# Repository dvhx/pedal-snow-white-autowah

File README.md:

# pedal-snow-white-autowah
Snow White AutoWah (envelope filter) guitar pedal in 125B enclosure using layout without offboard-wiring

# Features

- 125B enclosure
- Top mounted jacks
- Center-negative DC barrel jack
- Perfect pedal layout:
    - one big pcb
    - no offboard wiring
    - easy insertion into enclosure
    - easy testing outside of enclosure (including pots and stomp switch!)
- Included:
    - KiCad 7 project (schematic, PCB, pot daugterboards)
    - Gerber files
    - Artwork

# Sample

- [Short sample on Youtube](https://www.youtube.com/embed/3BYL_riq4po)

# Schematic

# PCB

# Gerbers

- [gerbers.zip](https://raw.githubusercontent.com/dvhx/pedal-snow-white-autowah/refs/heads/master/kicad/gerbers.zip) - main PCB
- [gerbers-pots.zip](https://raw.githubusercontent.com/dvhx/pedal-snow-white-autowah/refs/heads/master/kicad_pot_daugterboard/gerbers-pots.zip) - pot daugterboards (you can also use perfboard or stripboard)

# BOM

Most of the parts is available at LCSC. At [https://www.lcsc.com/bom](https://www.lcsc.com/bom) you can import
this CSV file: [kicad/bom/bom_lcsc_autowah.csv](kicad/bom/bom_lcsc_autowah.csv), the price is approx. $17,
if you are building more than 1 pedal increase the amount of LM13700, audio jacks and opamps.
All other parts should be enough for 5 pedals due to minimal ordering quantity.

The rest of the parts is available on aliexpress:

- [50kB Pot, $0.80/pcs](https://s.click.aliexpress.com/e/_c3w9c93V)
- [1MC Pot, $0.80/pcs](https://s.click.aliexpress.com/e/_c3w9c93V)
- [50kB Pot, $0.80/pcs](https://s.click.aliexpress.com/e/_c3w9c93V)
- [100kB Pot, $0.80/pcs](https://s.click.aliexpress.com/e/_c3w9c93V)
- [Pot knobs, $1/10pcs](https://s.click.aliexpress.com/e/_c4n3mVNp)
- [2x Lightpipe, $0.285/pcs](https://www.aliexpress.com/item/1005010409920827.html)
- [Model Enclosure_125B, $7.85/pcs](https://s.click.aliexpress.com/e/_c33GoZ8r)
- [Switch_3P2T Switch_3PDT, $2.13/pcs](https://s.click.aliexpress.com/e/_c2vpDqzN)
- [0805 resistor kit, $4.18/1500pcs/60values](https://s.click.aliexpress.com/e/_c4WAuc7p)
- [0805 capacitor kit, $4.51/720pcs/36values](https://s.click.aliexpress.com/e/_c3UD8Gzd)

Total parts cost including shipping, PCB manufacturing, enclosure, spray paint and artwork sticker is approx $50.

# Photos

## PCB

## Enclosure

# Build instructions

- Visually check PCB for defects
- Chect for short on tip and sleeve pins of JDC1
- Power section
    - Solder GND wire loop connector (0.5~0.8mm tined copper wire) in top-right corner, it is used for crocodile clip on negative lead of multimeter
    - Solder JDC1 barrel jack connector and measure 9V on R96 pads against ground (note that this PCB uses center negative 9V DC connector)
    - Solder R96 10R (values 0-47R are ok, expected load is 15mA so voltage drop is R*0.015, e.g. 10R = 0.15V drop (from 9V), 47R=0.47V)
    - Polarity protection
        - Solder Q99 AO3401, marking A19T (P-ch mosfet)
        - Solder ZD99 9.1V zenner BZT52B9V1S, marking 2WE (any zenner from 3-12V can be used), line is cathode = tip of the white triangle
        - Solder R99 10k (some recommend 100k, with 10k reverse transient is shorter and smaller, but forward current draw is higher, depending on zener)
        - Test polarity protection
            - Connect regulated power supply via JDC1. Use one ammeter (in series) and one voltmeter (negative lead to GND loop testpoint, positive lead to + pin of LED D99)
            - Start at 0V and slowly rise the voltage to 9V, the voltage on D99 should closely follow the input voltage.
                 Current should be small as there is no load, few microamps.
                 Depenging on your zener it can be up to Vin/R99, e.g. at 9V/10k=900uA, mine was 400uA with 10k R99
            - Return to 0V and raise negative voltage to -9V. Output should be 0V (I have -0.07V, probably leakage of zener diode, mosfet and voltmeter itself).
            - When you try positive voltage now it should still works.
    - In front of the JDC1 there are 2 holes, you can solder 0.5mm tined copper wire loop across and over the top of the JDC1 connector to reduce the side-to-side strain
    - Solder "Power on" red LED D99 and it's current limiting resistor R98 (4k7).
    - Power it via ammeter (consumption could be 1.5mA), test point +9V (next to C99) should have approx. 9V
    - Power it with reverse polarity, current should be zero, voltage should be near zero, led should be off, reconnect normally and it should work again
    - Solder blue D98 led and it's resistor R97 22k
    - Solder C99 electrolytic cap
- True bypass
    - Cut 0.3mm of the plastic from the front left corner of the JOUT1 and front right corner of the JIN1 jacks
    - Solder JIN, JOUT jacks, make sure of 4 things:
        - Cut corners are on the outside
        - Holes are in front
        - Jacks are on top side
        - They are well seated
    - Solder main 3P2T switch (on top side, well seated)
    - Test with guitar and power on, when effect is off it should work as true bypass, when the effect is off you should not hear anything.
        Or use continuity tester, when efect is on, JIN shorts to IN, JOUT shorts to OUT.
        When effect is off JIN shorts to JOUT and IN shorts to ground
- Solder JGND1 and test if it goes easily into enclosure, but still should be touching it, making contact, bend the contact more/less to adjust the force.
- If you ever plan to use internal battery (or sell the pedal), solder U99 JST-XH connector and test it now. The power on led will only shine if the input audio mono jack is in.
  When you connect DC barrel jack the battery should be disconnected automatically. Battery connector is also reverse polarity protected.
- Drill the enclosure, Use spare pcb to mark where the holes will be.
    - 12.7mm hole for main 3PDT switch
- Solder 4 pots on their adapter boards. Before you solder them make sure that 3PDT switch have enough thread for given pot height.

    Note: I designed this before I knew actual height of everything so I had to make daughterboards from perfboard,
            but you can now use real PCB daugterboards: [kicad_pot_daugterboard/](kicad_pot_daugterboard/).
            The key issue to keep in mind is that the daugterboard is so tall that the top of the pot thread
            aligns with the top of the switch threads when the pot daughterboard is resting on the pcb.
            In my case, for my pots, it was exactly 4 holes on the perfboard.
            Make 4 identical daugterboards for the 4 pots but don't solder them yet into the pcb.
- Drill four 8mm holes for the pots.
    On the PCB there are 4 tiny non-plated through holes (NPTH) that are aligned with the axle of the pot, you can use this holes as a drill teplate for the enclosure.
    When you put pot with daugterboard on the side atop of the pcb you can see that the drill template holes are aligned with the pot axle, and that the pin header pins are
    aligned with the pot footprint holes where it will be then soldered.

    - Tape spare pcb to the top, use tiny NPTH holes to pre-drill with 1mm drill, then drill with 8mm drill for the pots (use do it in two steps, drill 4mm then 8mm)
    - Snip off the dimple in front of each pot (with side-cut pliers)
    - Insert PCB with all 4 pot daughterboards into enclosure, tighten 4 pot nuts and also tighten main switch nut (from the bottom use other nut as a stopper),
      then solder pot daugterboards into the pcb, this will be their final position be accurate
- Drill 10mm holes for 2 audio jacks (there are two holes marking center of axis of jacks, one is marked 17.72 which is distance from bottom of enclosure)
- Drill 10mm hole for DC barrel jack (simply 15.5mm from the bottom in the center)
- Drill 1 or 2 holes for light pipes (mine were 2.3mm, your may be different)
- Test the insertion into enclosure. Make the inserting as smooth and easy as possible at this stage so that you don't damage finished pedal later.
    The insertion should be effortless, everything should align and match perfectly (except for jgnd1 there should be a bit of friction).
- Virtual ground
    - solder C14 and measure 9V on it
    - solder R9, R10, C3, C4
    - measure that C3 has approximately 4.5V
    - measure power consumption of entire pedal with effect on (1.99mA at 9.00V)
    - put on ESD strap from now on
    - solder U2 opamp and measure that VG test point have approximately 4.5V
    - measure power consumption again, difference is the consumption of 1 opamp (3.13mA at 9.00V = 1.14mA per amplifier @9V)
    - load VG with 10k to ground and voltage should not drop too much (4.5 to maybe 4.49, the divider itself is not regulated so ...)
    - Measure +4.5V on every single opamp (U3, U6, U7) pin 3
    - Cleanup flux and check 4.5V on VG test point again
- Input buffer
    - With effect on, use audio probe to check that audio signal is on the IN testpoint
    - Measure 4.5V on R6 (upper pad)
    - Solder R1 and C19 and measure 9V on C19 (right pad)
    - Solder R4, R5, R6, R7, C2
    - Check that gate still has audio signal
    - Solder Q2 JFET
    - With effect on check audio on BUF test point, you should hear audio
    - Solder temporary wire between BUF and OUT test points, test pedal, it should now work as JFET buffer,
        when ON it should be brighter, with low impedance input on the pedal output (e.g. PC sound card mic input which has impedance approx. 1700 ohm)
        the difference should be significant, muddy with bypass, bright with effect on.
    - Remove the BUF-OUT temporary wire
    - Clean up the flux and check audio on BUF testpoint
- Sensitivity (extra gain stage for envelope detector)
    - Solder C1 and check 9V on it
    - Measure 4.5V on pin 3 of the opamp footprint
    - Measure good audio signal on left pin of C6
    - Solder C6, R11, C7
    - With Sensitivity pot in any position, you should hear audio on SEN test point (it is still in series so it doesn't work as voltage divider and doesn't attenuate)
    - make sure you still wearing esd strap
    - Solder opamp U3
    - Check audio on SEN test point, sensitivity pot should now be able to adjust volume from 0 to 5x louder
    - Measure power consumption (4.9mA)
    - Clean up the flux and check SEN test point and pot again
- Envelope detector
    - rotate SENS pot in the middle and check good audio on EDIN test point
    - Solder C18 and measure 9V on it
    - Solder R12 R13 D4 D5 and U6 opamp
    - When playing sinewave you should see bottom half of the sinewave on the test point ED1
        - Sinewave at EDIN

        - Signal at ED1 testpoint

    - Solder R14 and R17, ED1 (and top pin of C8) will now have saggy bottom signal:

    - Solder C15 and measure 9V on it
    - Solder R15 R16 C8 and U7 opamp
    - Measure consumption (6.6mA)
    - When you play simple strums, ED2 test point should already show envelope (lower the timebase of scope to see the envelope)
        Here is 3-strings strum decaying over 4s or so. Sensitivity to 11 o-clock. Amplitude is virtually full scale from 0 to almost 9V.

- Decay speed
    - Solder R18 D6 R19 C9
    - Testpoint DEC will show same envelope as ED2, but the decay will be slower or faster depending on the Decay pot position
        Note: Easiest way to test decay is use 1s sinewave, 3s silence. Then you clearly see fast decay at 0% and several second long decay on 100%.
- +5V regulator
    - Measure consumption (6.65mA)
    - Solder C17 and verify 9V on it
    - Solder C5 D3 and U4 regulator
    - verify +5V on the +5V test point
    - Measure consumption (9.60mA)
- Bias
    - Solder C20 and check +5V on it
    - Solder Q3, Q4, R21, R20
    - Testing this part is bit more difficult, you can leave it untested.
- Voltage controlled filter
    - Solder C16, C21 and measure 9V on it
    - Measure consumption (9.68mA)
    - Solder C10, C13, R22, R23, R24, R27, R31, R25, R26, R28, R32, R33
    - Measure consumption (10.54mA)
    - Without input singal and with pots at 12-o'clock measure pin voltages of LM13700 footprint (LM13700 not yet soldered, just a doublechceck)
        Pin1 = 5V (top left),
        Pin2 = 0V,
        Pin3 = 4.5V,
        Pin4 = 4.31V,
        Pin5 = 0V,
        Pin6 = 0V,
        Pin7 = 0V,
        Pin8 = 2.34V (bottom left),
        Pin9 = 2.15V (bottom right),
        Pin10 = 0V,
        Pin11 = 9V,
        Pin12 = 0V,
        Pin13 = 4.5V,
        Pin14 = 4.34V,
        Pin15 = 0V,
        Pin16 = 5V (top right)
    - Solder LM13700
    - Solder C11, C12
    - Measure consumption (12.2mA)
    - Pedal should now be completed and work
- Final testing
    - Put pedal in enclosure and do final test of the pedal

### Support

You can support development on [Patreon](https://www.patreon.com/DusanHalicky) or you can hire me via [Upwork](https://www.upwork.com/freelancers/~013b4c3d6e772fdb01)

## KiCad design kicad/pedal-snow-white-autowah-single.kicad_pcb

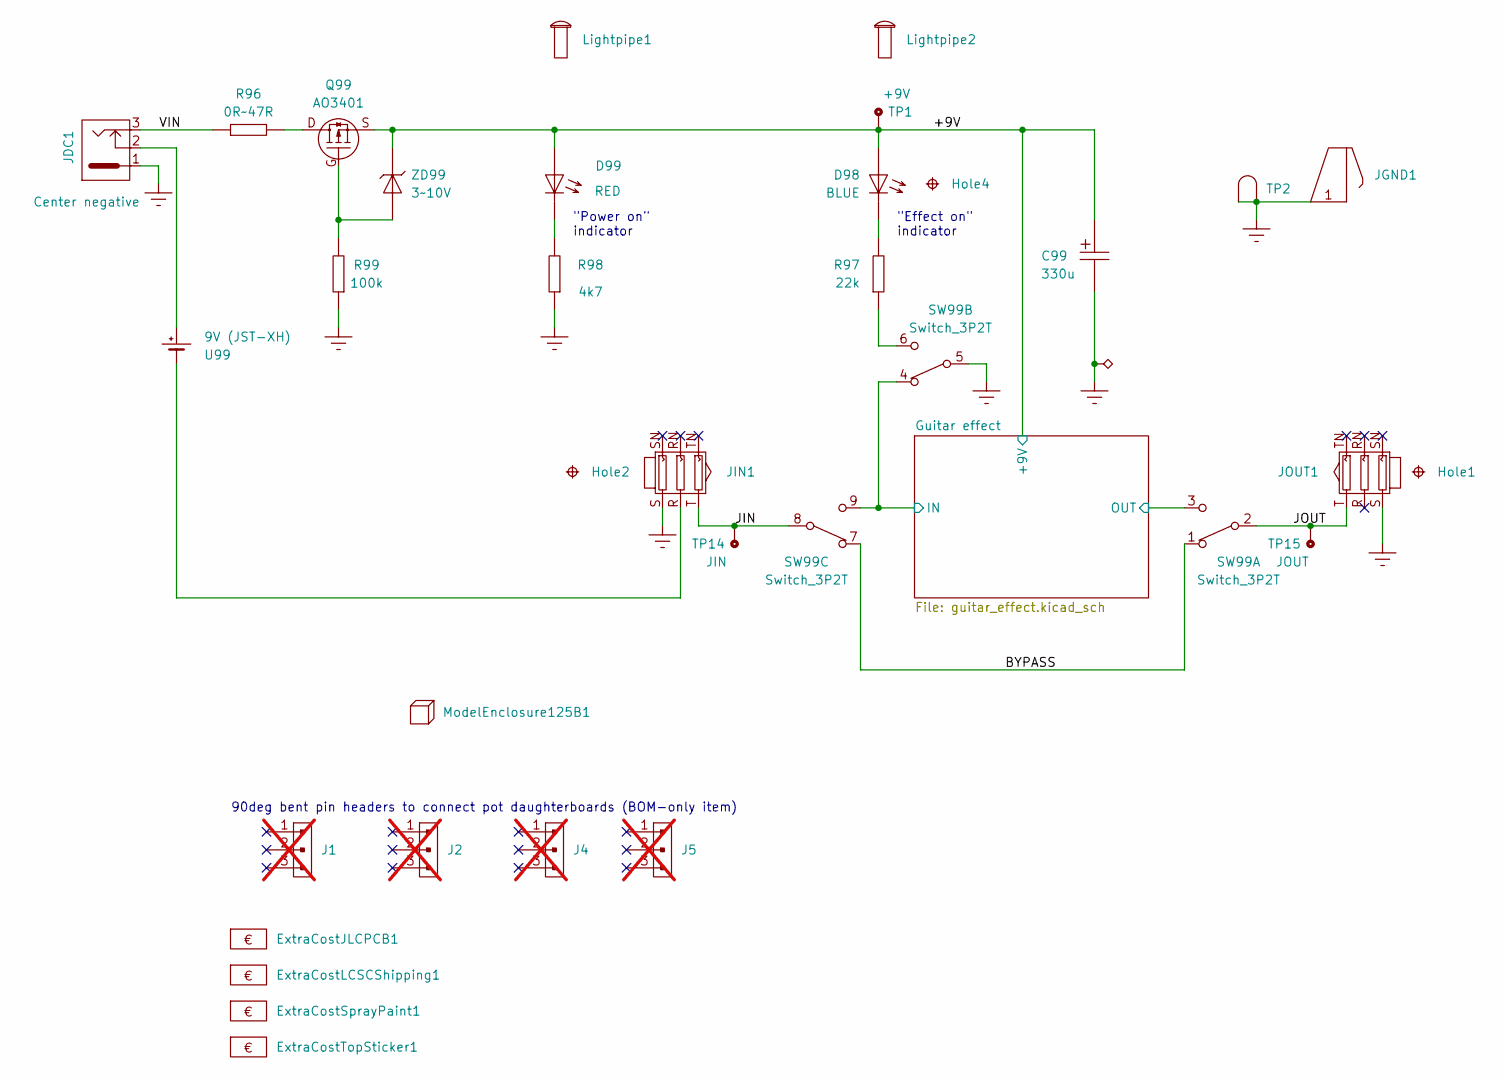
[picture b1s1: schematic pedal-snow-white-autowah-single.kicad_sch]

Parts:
C99: 330u; C_polarized_D6.35mm_H15mm_P2.54mm
D98: BLUE; D_LED_3mm
D99: RED; D_LED_3mm
ExtraCostJLCPCB1: ExtraCost
ExtraCostLCSCShipping1: ExtraCost
ExtraCostSprayPaint1: ExtraCost
ExtraCostTopSticker1: ExtraCost
Hole1, Hole2, Hole4: Hole; Hole_M2_isolated
J1, J2, J4, J5: Header_1x3_male; Header_1x3_male_bent; not fitted
JDC1: Connector_DC_jack_3pin; Connector_DC_005_2.0
JGND1: Keystone_590
JIN1: Connector_Jack_6.35mm_female_stereo
JOUT1: Connector_Jack_6.35mm_female_stereo
Lightpipe1, Lightpipe2: Lightpipe
ModelEnclosure125B1: Model; Enclosure_125B
Q99: AO3401; SOT23-GSD
R96: 0R~47R; R_0805
R97: 22k; R_0805
R98: 4k7; R_0805
R99: 100k; R_0805
SW99: Switch_3P2T; Switch_3PDT
TP1, TP14, TP15: Test_point_D1.5_H0.5; Test_point_1.5mm_H0.5mm
TP2: Test_point_loop; Test_point_loop_2.54mm
U99: 9V (JST-XH); Battery_JST_XH_female_2pin
ZD99: 3~10V; D_SOD-323-V3

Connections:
/+9V: C99.P, D98.A, D99.A, Q99.S, TP1.1, ZD99.K; also elsewhere on the board
/BYPASS: SW99.1, SW99.7
/Guitar effect/IN: SW99.4, SW99.9; also elsewhere on the board
/Guitar effect/OUT: SW99.3; also elsewhere on the board
/JIN: JIN1.T, SW99.8, TP14.1
/JOUT: JOUT1.T, SW99.2, TP15.1; also elsewhere on the board
/VIN: JDC1.3, R96.1
GND: C99.N, JDC1.1, JGND1.1, JIN1.S, JOUT1.S, R98.1, R99.1, SW99.5, TP2.1, TP2.2; also elsewhere on the board
unnamed: D98.K, R97.2
unnamed: D99.K, R98.2
unnamed: JDC1.2, U99.P
unnamed: JIN1.R, U99.N
unnamed: Q99.D, R96.2
unnamed: Q99.G, R99.2, ZD99.A
unnamed: R97.1, SW99.6

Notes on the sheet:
"Effect on" indicator
90deg bent pin headers to connect pot daughterboards (BOM-only item)
"Power on" indicator

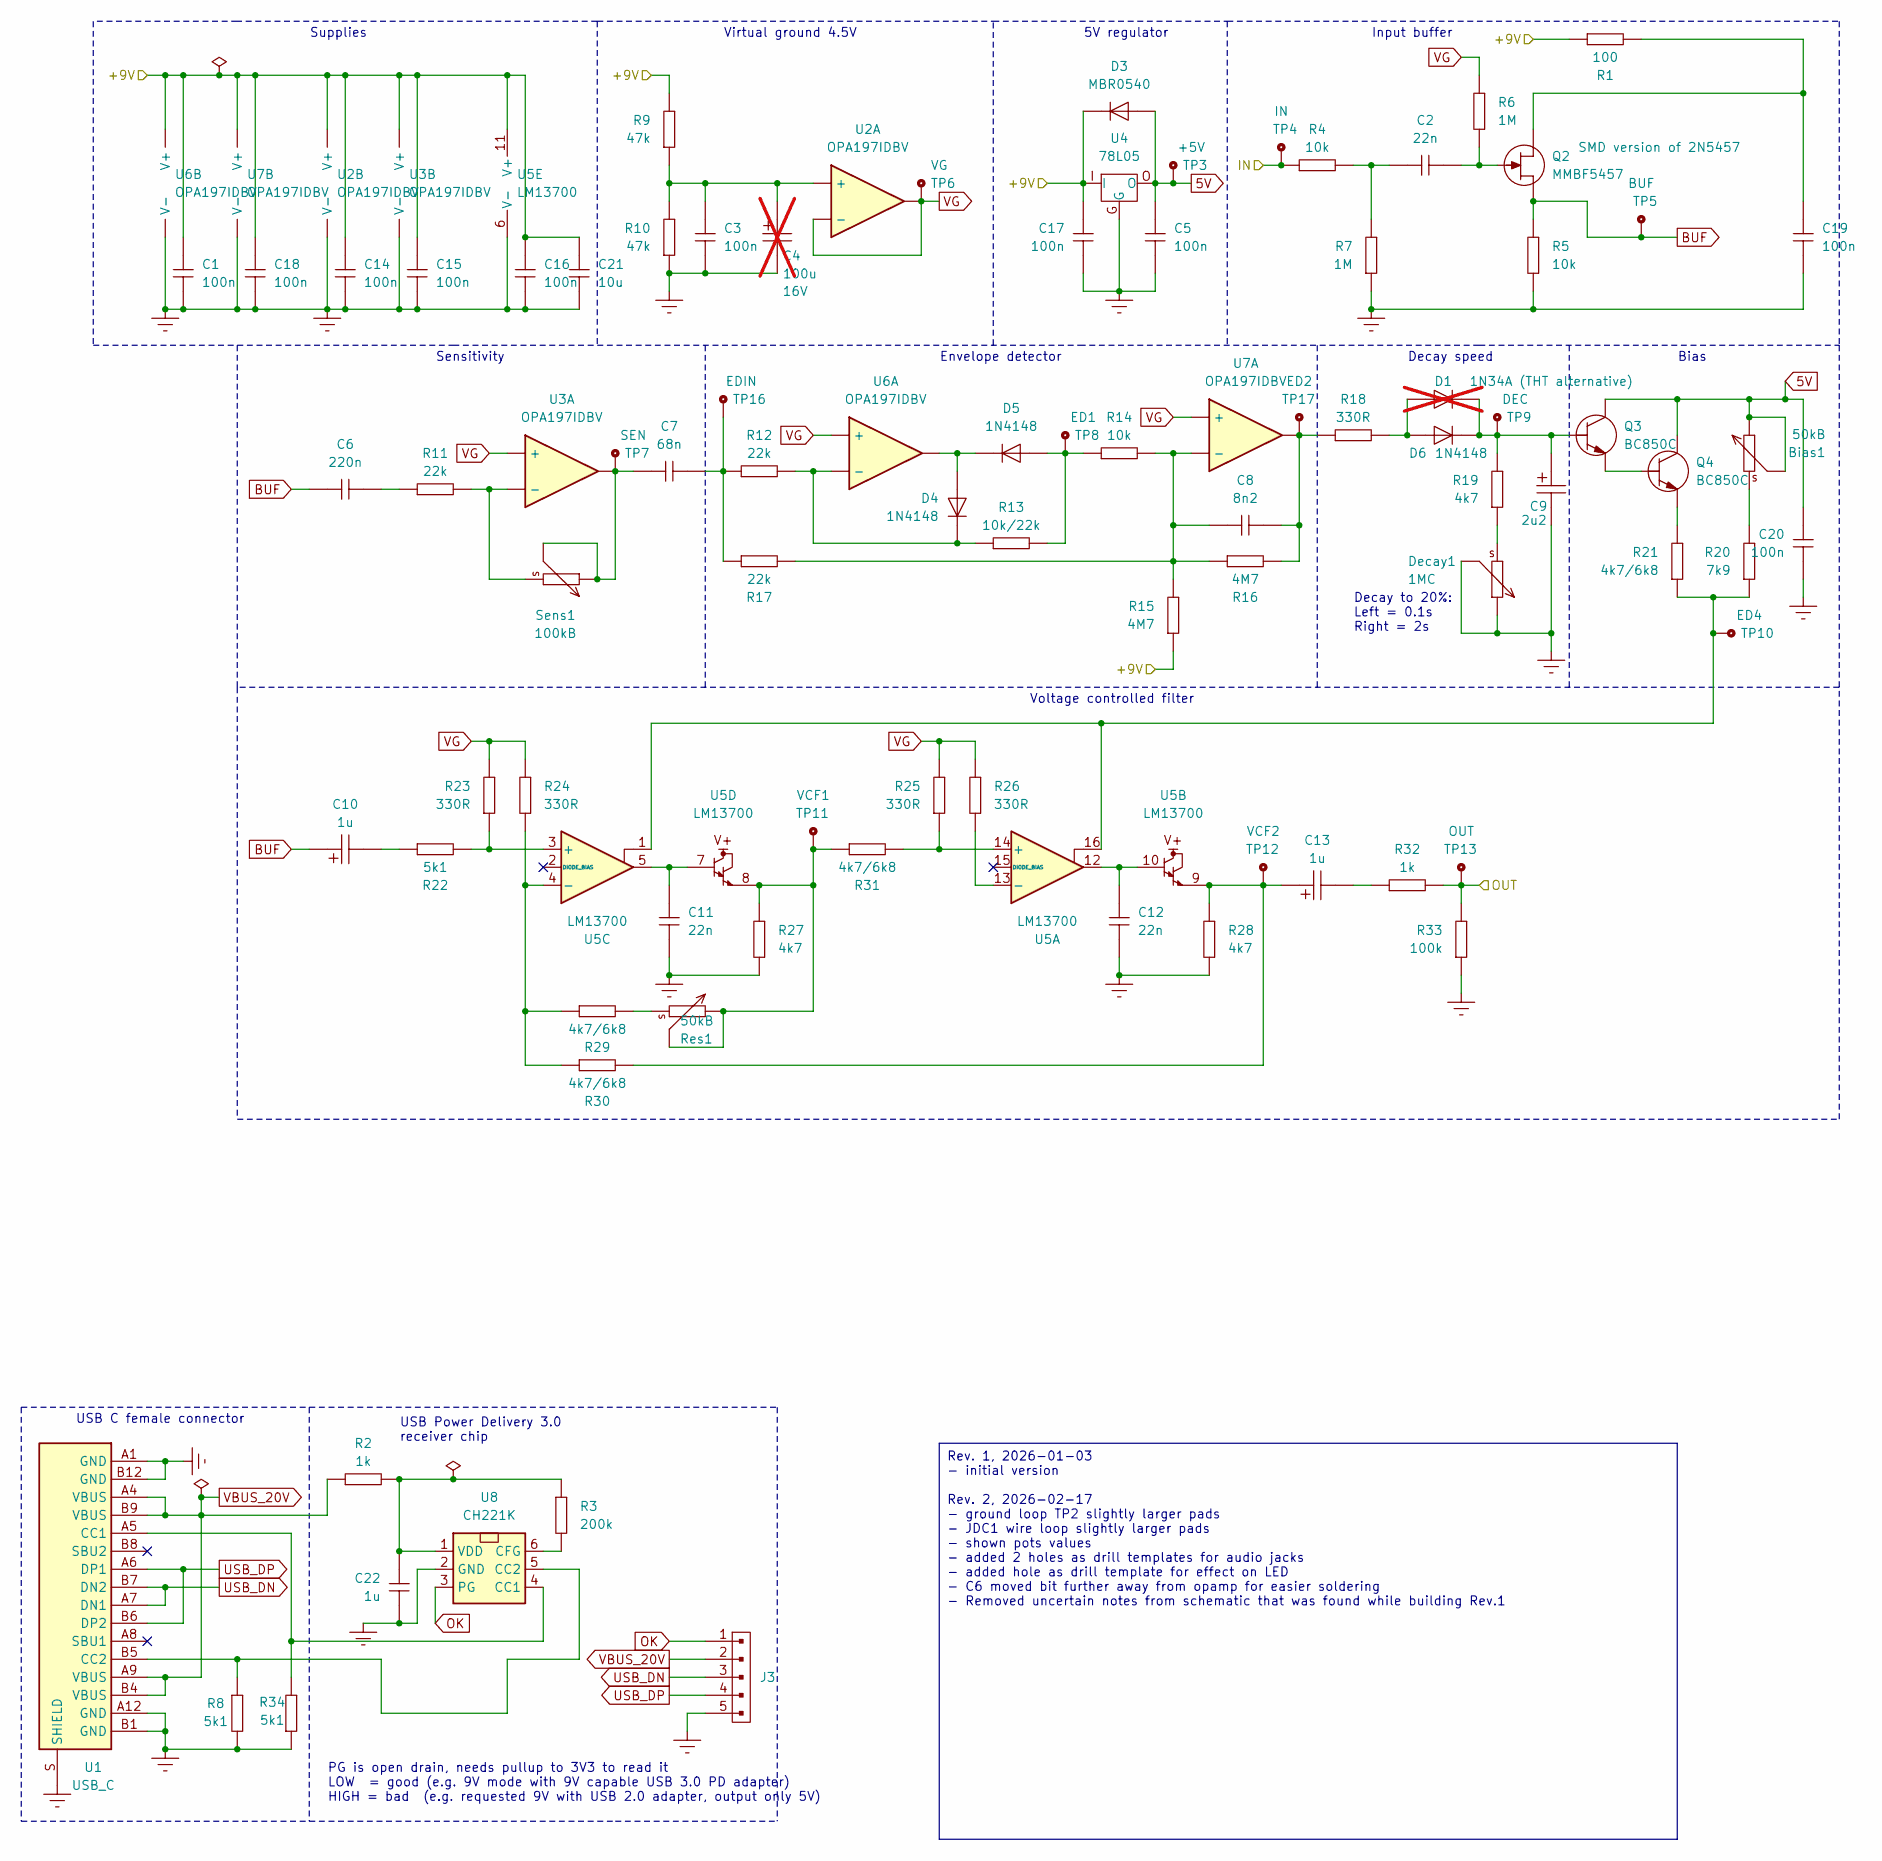
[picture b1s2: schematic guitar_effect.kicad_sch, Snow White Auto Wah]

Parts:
Bias1: 50kB; P_Daughterboard_Mono_Davies_1900H
C1, C3, C5, C14, C15, C16, C17, C18, C19, C20: 100n; C_0805
C2, C11, C12: 22n; C_foil_W7.2H6.5T2.5P5.08D0.45mm
C4: 100u; C_polarized_D5mm_H12mm_P2mm; not fitted
C6: 220n; C_foil_W7.2H6.5T2.5P5.08D0.45mm
C7: 68n; C_foil_W7.2H6.5T2.5P5.08D0.45mm
C8: 8n2; C_foil_W7.2H6.5T2.5P5.08D0.45mm
C9: 2u2; C_polarized_D4H7P2D0.45mm
C10, C13: 1u; C_polarized_D4H7P2D0.45mm
C21: 10u; C_0805
C22: 1u; C_0603
D1: 1N34A (THT alternative); D_DO-35_cathode_down; not fitted
D3: MBR0540; D_SOD-123
D4, D5, D6: 1N4148; D_SOD-323-V3
Decay1: 1MC; P_Daughterboard_Mono_Davies_1900H
J3: Header_1x5_male; Header_1x5_male_upright
Q2: MMBF5457; SOT23-DSG
Q3, Q4: BC850C; SOT23-BEC
R1: 100; R_0805
R2: 1k; R_0603
R3: 200k; R_0603
R4, R5, R14: 10k; R_0805
R6, R7: 1M; R_0805
R8, R34: 5k1; R_0603
R9, R10: 47k; R_0805
R11, R12, R17: 22k; R_0805
R13: 10k/22k; R_0805
R15, R16: 4M7; R_0805
R18, R23, R24, R25, R26: 330R; R_0805
R19, R27, R28: 4k7; R_0805
R20: 7k9; R_0805
R21, R29, R30, R31: 4k7/6k8; R_0805
R22: 5k1; R_0805
R32: 1k; R_0805
R33: 100k; R_0805
Res1: 50kB; P_Daughterboard_Mono_Davies_1900H
Sens1: 100kB; P_Daughterboard_Mono_Davies_1900H
TP3, TP4, TP5, TP6, TP7, TP8, TP9, TP10, TP11, TP12, TP13, TP16, TP17: Test_point_D1.5_H0.5; Test_point_1.5mm_H0.5mm
U1: USB_C; USB_C_Receptacle_HRO_TYPE-C-31-M-12
U2, U3, U6, U7: OPA197IDBV; SOT23-5-OGPNV-V2
U4: 78L05; SOT-89-3-OGI
U5: LM13700; SOP-16_4.4x10.4mm_P1.27mm
U8: CH221K; SOT23-6

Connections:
5V: Bias1.E, Bias1.W, C5.1, C20.1, D3.A, Q3.C, Q4.C, TP3.1, U4.O
/+9V: C1.1, C14.1, C15.1, C16.1, C17.1, C18.1, C21.1, D3.K, R1.1, R9.2, R15.1, U2.V (V+), U3.V (V+), U4.I, U5.11 (V+), U6.V (V+), U7.V (V+); also elsewhere on the board
/Guitar effect/IN: R4.1, TP4.1; also elsewhere on the board
/Guitar effect/OUT: R32.2, R33.2, TP13.1; also elsewhere on the board
BUF: C6.2, C10.P, Q2.S, R5.2, TP5.1
GND: C1.2, C3.2, C4.N, C5.2, C9.N, C11.2, C12.2, C14.2, C15.2, C16.2, C17.2, C18.2, C19.2, C20.2, C21.2, C22.2, Decay1.E, Decay1.W, J3.5, R5.1, R7.1, R8.2, R10.1, R27.1, R28.1, R33.1, R34.1, U1.A1 (GND), U1.A12 (GND), U1.B1 (GND), U1.B12 (GND), U1.S (SHIELD), U2.G (V-), U3.G (V-), U4.G, U5.6 (V-), U6.G (V-), U7.G (V-), U8.2 (GND); also elsewhere on the board
unnamed: Bias1.S, R20.2
unnamed: C2.1, Q2.G, R6.1
unnamed: C2.2, R4.2, R7.2
unnamed: C6.1, R11.1
unnamed: C7.1, R12.1, R17.1, TP16.1
unnamed: C7.2, Sens1.E, Sens1.W, TP7.1, U3.O
unnamed: C8.1, R16.2, R18.1, TP17.1, U7.O
unnamed: C9.P, D1.K, D6.K, Q3.B, R19.2, TP9.1
unnamed: C10.N, R22.1
unnamed: C11.1, U5.5, U5.7
unnamed: C12.1, U5.10, U5.12
unnamed: C13.N, R32.1
unnamed: C13.P, R28.2, R30.2, TP12.1, U5.9
unnamed: C19.1, Q2.D, R1.2
unnamed: D1.A, D6.A, R18.2
unnamed: D4.A, D5.K, U6.O
unnamed: D5.A, R13.2, R14.1, TP8.1
unnamed: Decay1.S, R19.1
unnamed: Q3.E, Q4.B
unnamed: Q4.E, R21.2
unnamed: R20.1, R21.1, TP10.1, U5.1, U5.16
unnamed: R27.2, R31.1, Res1.E, Res1.W, TP11.1, U5.8
unnamed: R29.2, Res1.S
unnamed: R34.2, U1.A5 (CC1), U8.4 (CC1)
unnamed: R8.1, U1.B5 (CC2), U8.5 (CC2)
unnamed: C3.1, C4.P, R9.1, R10.2, U2.P (+)
unnamed: R11.2, Sens1.S, U3.N (-)
unnamed: R25.1, R31.2, U5.14 (+)
unnamed: R26.1, U5.13 (-)
unnamed: R22.2, R23.1, U5.3 (+)
unnamed: R24.1, R29.1, R30.1, U5.4 (-)
unnamed: D4.K, R12.2, R13.1, U6.N (-)
unnamed: C8.2, R14.2, R15.2, R16.1, R17.2, U7.N (-)
unnamed: R3.2, U8.6 (CFG)
unnamed: C22.1, R2.2, R3.1, U8.1 (VDD)
OK: J3.1, U8.3 (PG)
USB_DN: J3.3, U1.A7 (DN1), U1.B7 (DN2)
USB_DP: J3.4, U1.A6 (DP1), U1.B6 (DP2)
VBUS_20V: J3.2, R2.1, U1.A4 (VBUS), U1.A9 (VBUS), U1.B4 (VBUS), U1.B9 (VBUS)
VG: R6.2, R23.2, R24.2, R25.2, R26.2, TP6.1, U2.N (-), U2.O, U3.P (+), U6.P (+), U7.P (+)

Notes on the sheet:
Rev. 1, 2026-01-03 - initial version Rev. 2, 2026-02-17 - ground loop TP2 slightly larger pads - JDC1 wire loop slightly larger pads - shown pots values - added 2 holes as drill templates for audio jacks - added hole as drill template for effect on LED - C6 moved bit further away from opamp for eas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
Input buffer
Virtual ground 4.5V
Decay to 20%: Left = 0.1s Right = 2s
PG is open drain, needs pullup to 3V3 to read it LOW = good (e.g. 9V mode with 9V capable USB 3.0 PD adapter) HIGH = bad (e.g. requested 9V with USB 2.0 adapter, output only 5V)
Decay speed
Envelope detector
Voltage controlled filter
USB Power Delivery 3.0 receiver chip
Bias
5V regulator
USB C female connector
Sensitivity
Supplies

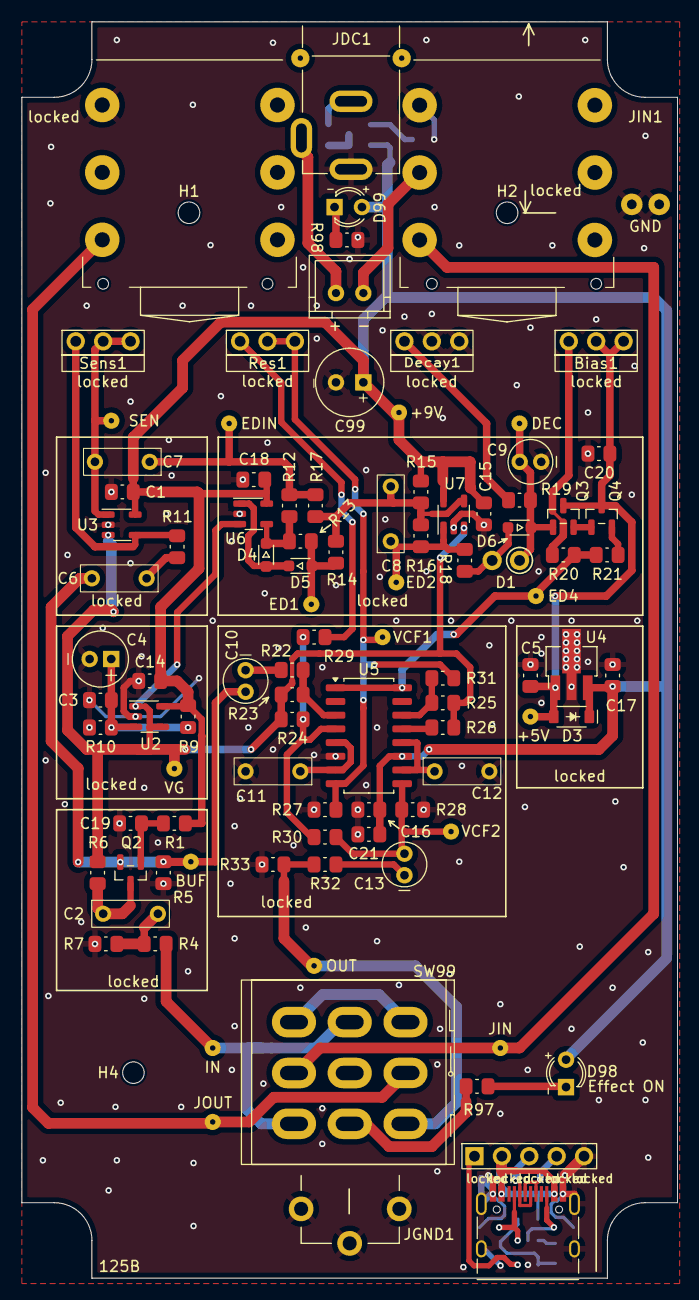
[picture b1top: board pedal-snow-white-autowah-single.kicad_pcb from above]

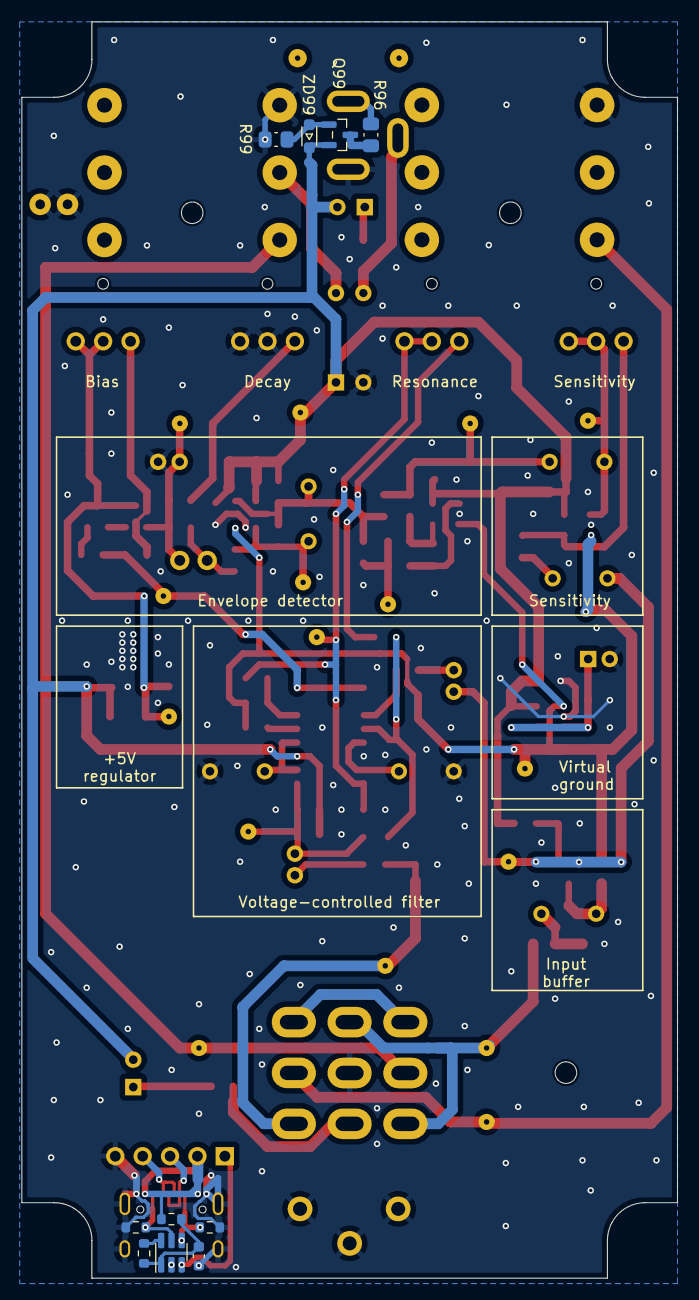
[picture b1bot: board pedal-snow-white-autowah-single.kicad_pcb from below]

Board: 2 copper layers, 60.8 x 116.5 mm, 113 parts (10 on the bottom side), 57 nets.

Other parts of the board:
locked: Connector_Jack_6.35mm_female_stereo

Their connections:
/JOUT: locked.T; also elsewhere on the board
GND: locked.S; also elsewhere on the board

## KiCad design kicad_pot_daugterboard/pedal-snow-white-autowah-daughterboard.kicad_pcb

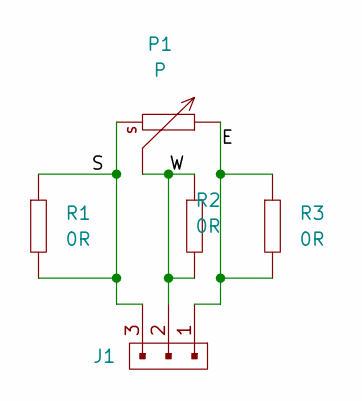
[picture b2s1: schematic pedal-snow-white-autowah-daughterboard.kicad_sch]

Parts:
J1: Header_1x3_male; Header_1x3_male_bent
P1: P; P_RV097NH_bent_pins
R1, R2, R3: 0R; R_0805

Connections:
/E: J1.1, P1.E, R3.1, R3.2
/S: J1.3, P1.S, R1.1, R1.2
/W: J1.2, P1.W, R2.1, R2.2

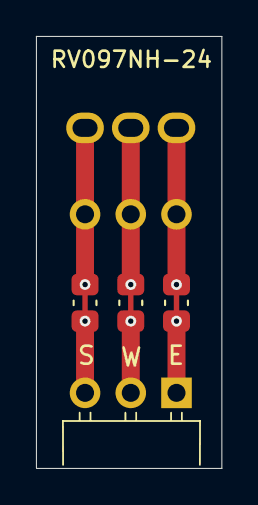
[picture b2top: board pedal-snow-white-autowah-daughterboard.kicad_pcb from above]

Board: 2 copper layers, 10.3 x 24.0 mm, 5 parts (1 on the bottom side), 3 nets.

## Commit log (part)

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2026-02-27 Test image thumbnails
2026-02-27 Added thumbnails
2026-02-27 Updated images
2026-02-27 Fixed thumbnails extensions
2026-02-27 Cleanup build instructions
2026-02-27 Added schematic
2026-02-27 Larger schematic thumbnails
2026-02-27 Larger thumbnails
2026-02-27 PCB photos
2026-02-27 PCB images
2026-02-27 Added pots daugterboards
2026-02-27 Pot dbs
2026-02-27 Larger photo
2026-02-27 Readme
2026-02-27 Larger image
2026-02-27 Added kicad files
2026-02-27 Gerbers for pots
2026-02-27 Links to gerbers
2026-02-27 Fixed gerbers links
2026-02-27 Added artwork
2026-02-28 Added bom
2026-02-28 Fixed bom link
2026-02-28 Fixed link
2026-02-28 Cost estimate
2026-02-28 YT video
2026-02-28 Added Patreon username for funding support
2026-02-28 Fixed kicad 3d models
2026-02-28 Fixed 3PDT switch model
2026-03-02 Better pcb picture
2026-03-02 Fixed pcb link
2026-03-02 Fixed missing 0603 resistor 3d model
2026-03-14 Added R, C parts to BOM
2026-03-14 Added pot knobs to BOM
